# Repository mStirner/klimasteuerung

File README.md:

# Klimasteuerung
Auswertung von Reedkontakten an Fenstern zu Freigabe/Steuerung einer Klimaanlage.

# Schaltplan

<small>[Schaltplan](./v2/Schaltplan.pdf) als PDF</small>

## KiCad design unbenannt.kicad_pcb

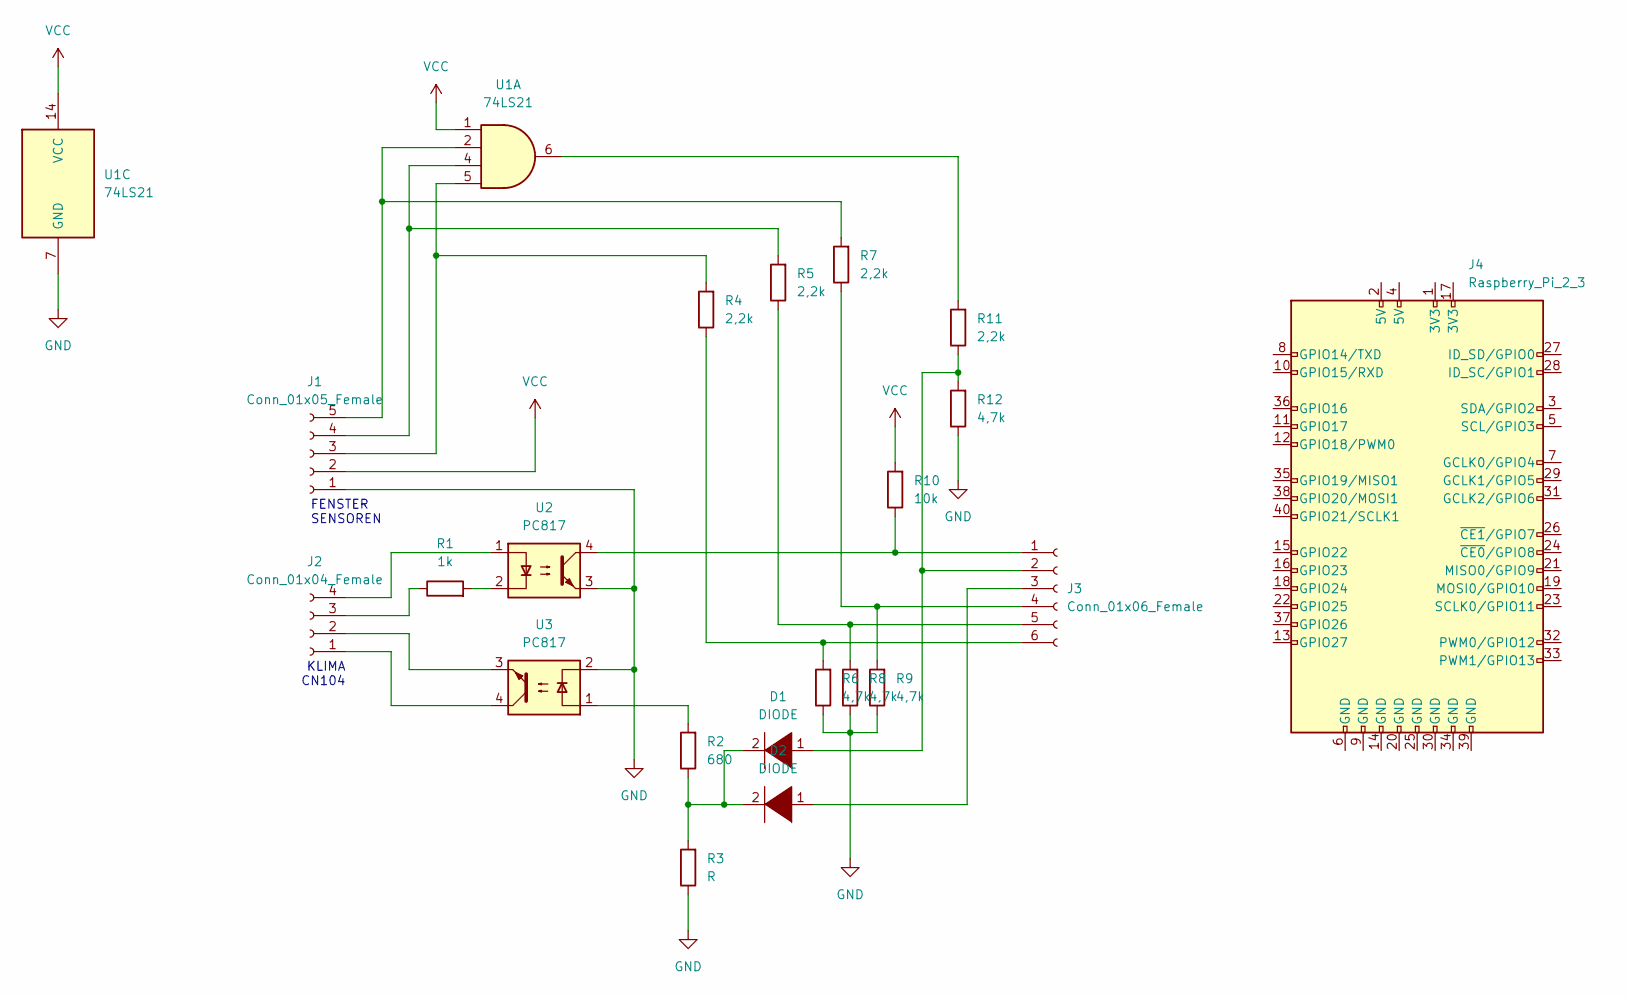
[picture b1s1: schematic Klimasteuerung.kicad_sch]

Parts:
D1, D2: DIODE; R_Axial_DIN0411_L9.9mm_D3.6mm_P15.24mm_Horizontal
J1: Conn_01x05_Female; PinHeader_1x05_P1.27mm_Vertical
J2: Conn_01x04_Female; PinHeader_1x04_P1.27mm_Vertical
J3: Conn_01x06_Female; PinHeader_1x06_P1.27mm_Vertical
J4: Raspberry_Pi_2_3
R1: 1k; R_Axial_DIN0411_L9.9mm_D3.6mm_P15.24mm_Horizontal
R2: 680; R_Axial_DIN0411_L9.9mm_D3.6mm_P15.24mm_Horizontal
R3: R; R_Axial_DIN0411_L9.9mm_D3.6mm_P15.24mm_Horizontal
R4, R5, R7, R11: 2,2k; R_Axial_DIN0411_L9.9mm_D3.6mm_P15.24mm_Horizontal
R6, R8, R9, R12: 4,7k; R_Axial_DIN0411_L9.9mm_D3.6mm_P15.24mm_Horizontal
R10: 10k; R_Axial_DIN0411_L9.9mm_D3.6mm_P15.24mm_Horizontal
U1: 74LS21; DIP-14_W7.62mm
U2, U3: PC817; DIP-4_W7.62mm

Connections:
GND: J1.1, R3.1, R6.1, R8.1, R9.1, R12.1, U1.7 (GND), U2.3, U3.2
unnamed: D1.1 (K), J3.2, R11.1, R12.2
unnamed: D1.2 (A), D2.2 (A), R2.1, R3.2
unnamed: D2.1 (K), J3.3
unnamed: J1.3, R4.2, U1.5
unnamed: J1.4, R5.2, U1.4
unnamed: J1.5, R7.2, U1.2
unnamed: J2.1, U3.4
unnamed: J2.2, U3.3
unnamed: J2.3, R1.1
unnamed: J2.4, U2.1
unnamed: R1.2, U2.2
unnamed: R2.2, U3.1
unnamed: J3.6, R4.1, R6.2
unnamed: J3.5, R5.1, R8.2
unnamed: J3.4, R7.1, R9.2
unnamed: J3.1, R10.1, U2.4
unnamed: R11.2, U1.6
VCC: J1.2, R10.2, U1.1, U1.14 (VCC)

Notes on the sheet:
KLIMA CN104
FENSTER SENSOREN

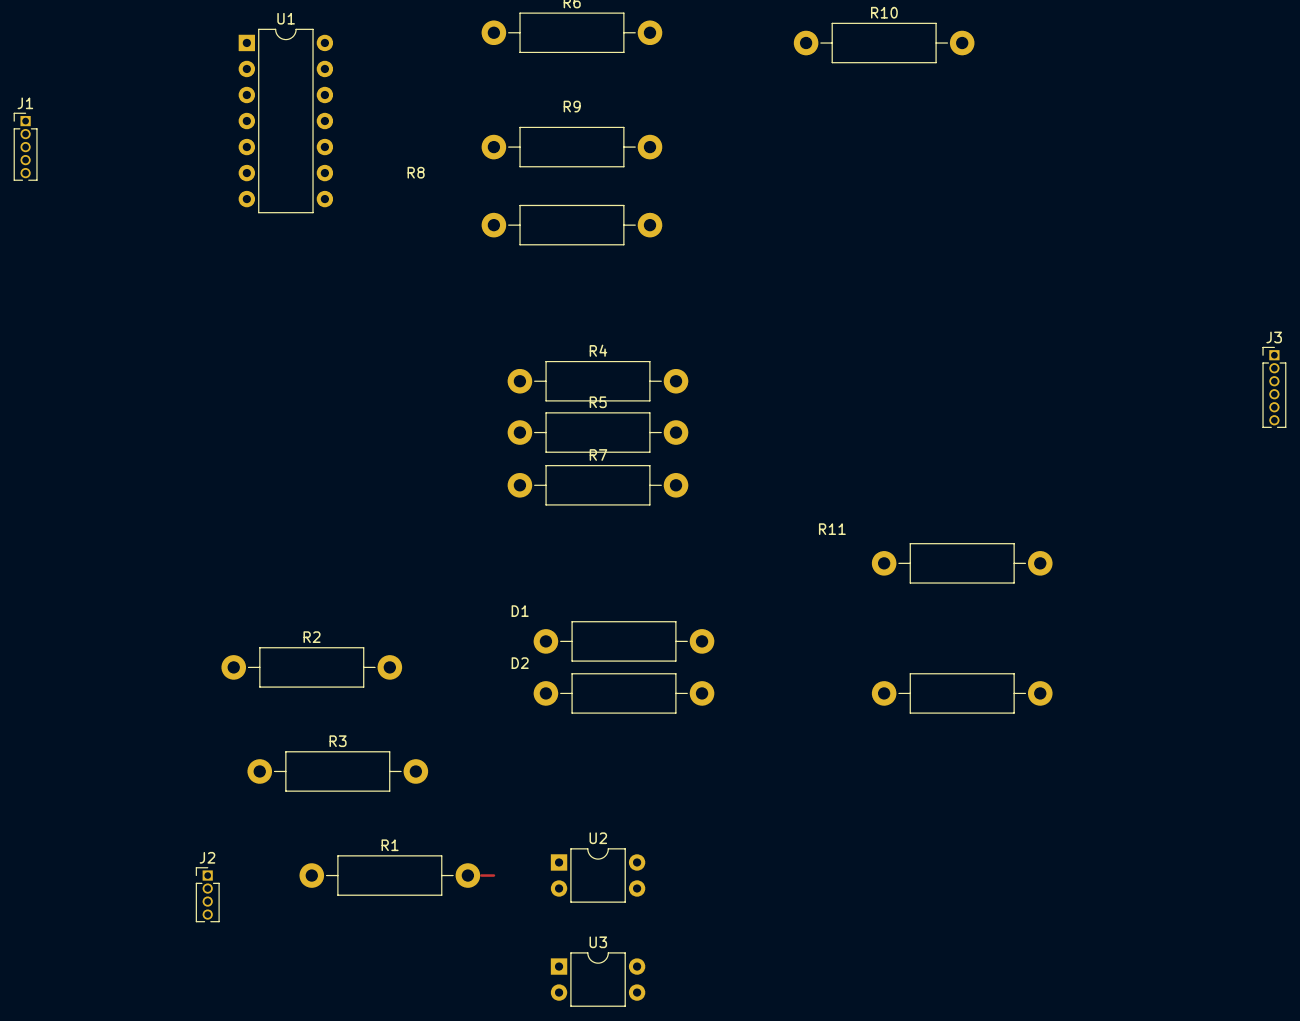
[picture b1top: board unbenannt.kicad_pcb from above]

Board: 2 copper layers, 20 parts (0 on the bottom side), 19 nets.

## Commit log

2024-09-09 init
2024-09-12 added v2
2024-09-13 moved
2024-09-14 adjustments to schematic
